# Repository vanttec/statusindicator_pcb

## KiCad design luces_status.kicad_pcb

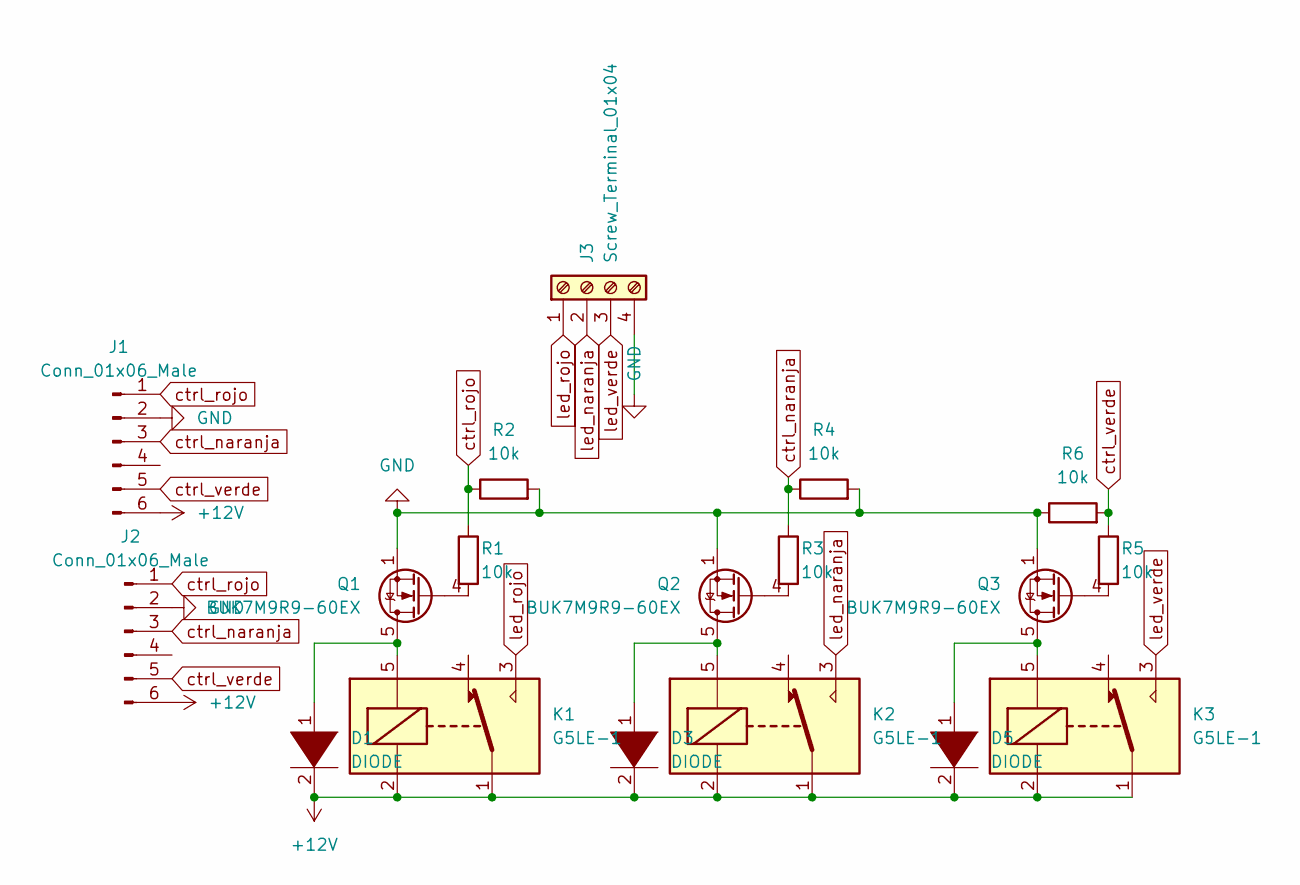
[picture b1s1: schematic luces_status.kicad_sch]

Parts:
D1, D3, D5: DIODE; Nexperia_CFP3_SOD-123W
J1: Conn_01x06_Male; PinHeader_2x03_P1.27mm_Vertical
J2: Conn_01x06_Male; PinHeader_2x03_P2.54mm_Vertical
J3: Screw_Terminal_01x04; TerminalBlock_Phoenix_MKDS-1,5-4-5.08_1x04_P5.08mm_Horizont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
K1, K2, K3: G5LE-1; Relay_SPDT_Omron-G5LE-1
Q1, Q2, Q3: BUK7M9R9-60EX; LFPAK33
R1, R2, R3, R4, R5, R6: 10k; R_0603_1608Metric

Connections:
+12V: D1.2 (A), D3.2 (A), D5.2 (A), J1.6, J2.6, K1.1, K1.2, K2.1, K2.2, K3.1, K3.2
GND: J1.2, J2.2, J3.4, Q1.1 (S), Q1.2 (S), Q1.3 (S), Q2.1 (S), Q2.2 (S), Q2.3 (S), Q3.1 (S), Q3.2 (S), Q3.3 (S), R2.2, R4.2, R6.1
unnamed: D1.1 (K), K1.5, Q1.5 (D)
unnamed: D3.1 (K), K2.5, Q2.5 (D)
unnamed: D5.1 (K), K3.5, Q3.5 (D)
unnamed: Q1.4 (G), R1.2
unnamed: Q2.4 (G), R3.2
unnamed: Q3.4 (G), R5.2
ctrl_naranja: J1.3, J2.3, R3.1, R4.1
ctrl_rojo: J1.1, J2.1, R1.1, R2.1
ctrl_verde: J1.5, J2.5, R5.1, R6.2
led_naranja: J3.2, K2.3
led_rojo: J3.1, K1.3
led_verde: J3.3, K3.3

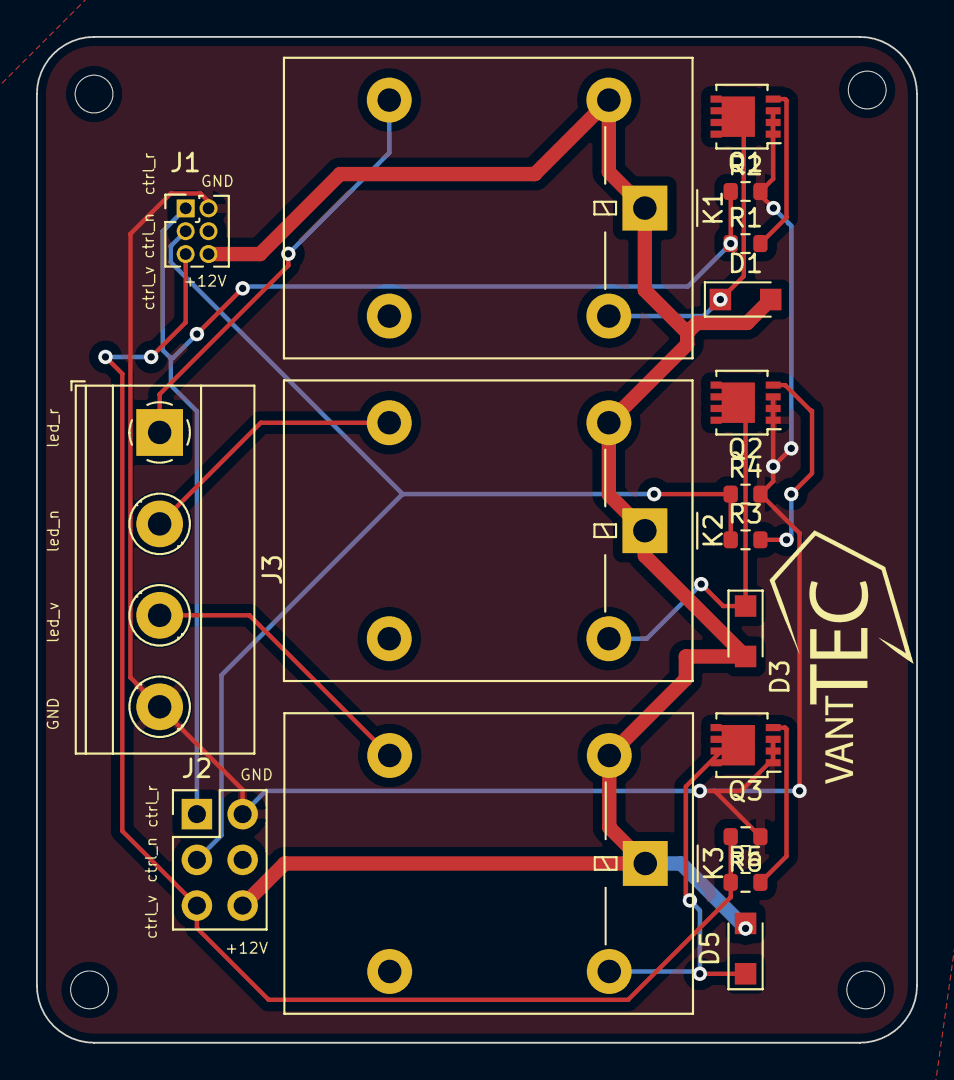
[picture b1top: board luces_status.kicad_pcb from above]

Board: 2 copper layers, 48.9 x 55.9 mm, 18 parts (0 on the bottom side), 14 nets.

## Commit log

2022-03-08 PCB de la torreta de status del barco
2022-03-29 Added rev A
